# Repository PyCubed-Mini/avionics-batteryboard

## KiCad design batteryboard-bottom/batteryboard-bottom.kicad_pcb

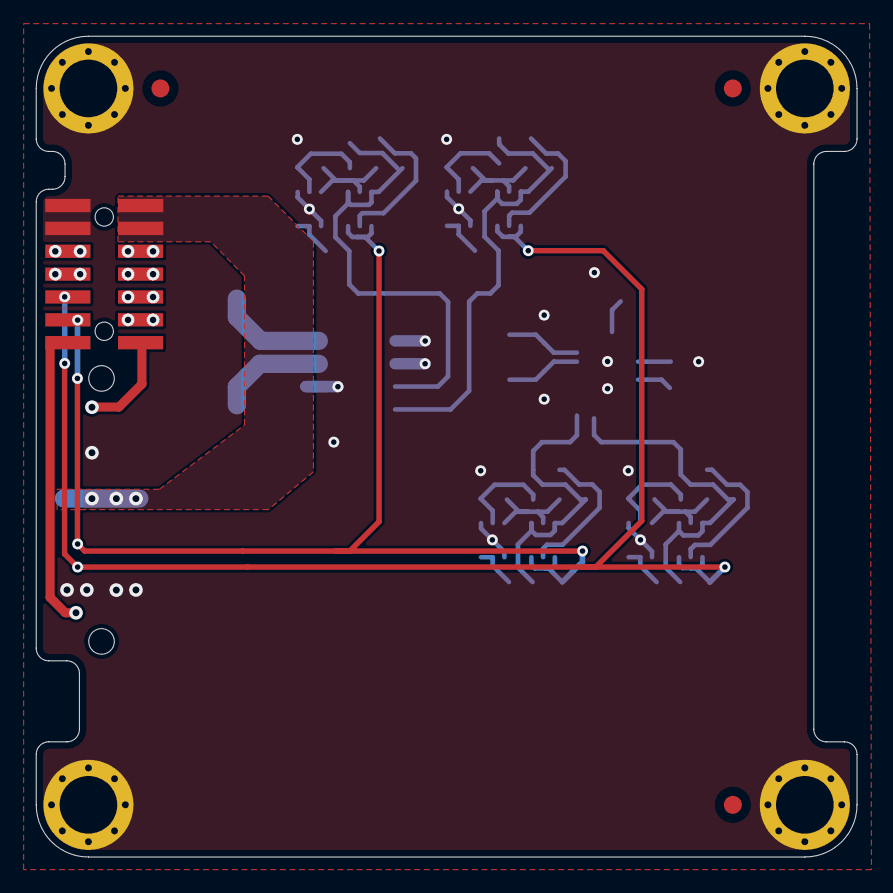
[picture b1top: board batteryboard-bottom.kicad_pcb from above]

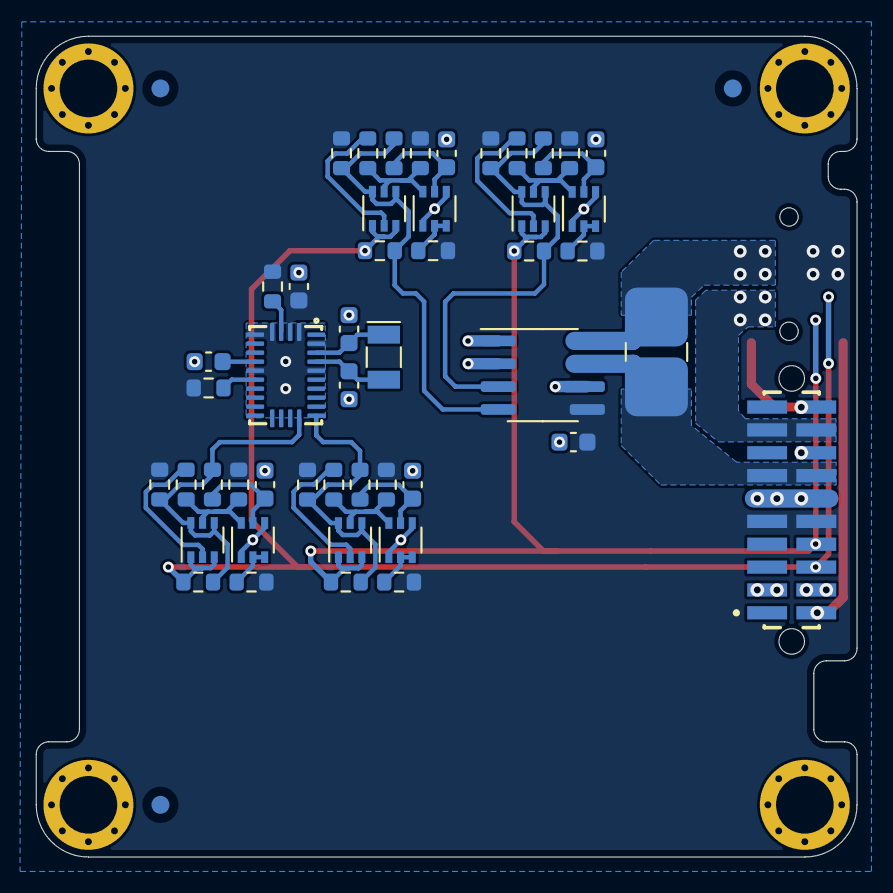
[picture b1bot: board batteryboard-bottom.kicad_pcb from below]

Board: 2 copper layers, 45.6 x 45.6 mm, 54 parts (48 on the bottom side), 35 nets.

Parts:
C1, C2, C8, C9: 10nF; C_0603_1608Metric
C3, C4, C5: 0.1uF; C_0603_1608Metric
C6, C7: 22pF; C_0603_1608Metric
H1, H2, H3, H4: MountingHole_Pad; MountingHole
J1: SFC-110-T2-X-D-A; SAMTEC_SFC-110-T2-X-D-A
J2: FTS-107-01-X-DV-A; SAMTEC-FTS-107-01-X-DV-A
Q1, Q3, Q5, Q7: NX3008NBKS; SOT-363_SC-70-6
Q2, Q4, Q6, Q8: MBT2222ADW1T1; SOT-363_SC-70-6
R1: 0.04R; R_2512_CurrentSense
R2, R7, R14, R21: 680R; R_0603_1608Metric
R3, R8, R15, R22: 100K; R_0603_1608Metric
R4, R5, R9, R10, R16, R17, R18, R19, R23, R24: 10K; R_0603_1608Metric
R6, R11, R20, R25: 200K; R_0603_1608Metric
R12, R13, R26, R27: DNI (0R); R_0603_1608Metric
Ref**: Val**; pycubed_mini_half
U1: INA219BxD; SOIC-8_3.9x4.9mm_P1.27mm
U2: BNO085; LGA-28
Y1: 32.768kHz/12.5pF; Crystal_SMD_MicroCrystal_CC7V-T1A-2Pin_3.2x1.5mm

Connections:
+3V3: C3.1, C4.1, J1.9, J1.10, J2.5, J2.7, R3.1, R4.1, R5.1, R8.1, R9.1, R10.1, R15.1, R16.2, R17.2, R18.1, R19.1, R22.1, R23.1, R24.1, U1.5 (VS), U2.3 (VDD), U2.28 (VDDIO)
BATT_N_SW: J1.11, J1.12, J2.2, J2.4
BATT_P: J1.17, J1.18, J2.10, J2.12
BATT_P_SENSE: J2.6, J2.8, R1.1, U1.8 (IN+)
BATT_P_SW: J1.13, J1.14, R1.2, U1.7 (IN-)
COIL5_N: J1.20, J2.14
COIL5_P: J1.2, J2.13
GND: C1.2, C2.2, C3.2, C4.2, C5.2, C6.1, C7.2, C8.2, C9.2, H1.1, H2.1, H3.1, H4.1, J1.3, J1.4, J1.16, J2.1, J2.3, Q1.1 (S2), Q1.4 (S1), Q3.1 (S2), Q3.4 (S1), Q5.1 (S2), Q5.4 (S1), Q7.1 (S2), Q7.4 (S1), U1.1 (A1), U1.2 (A0), U1.6 (GND), U2.2 (GND), U2.5 (PS1), U2.6 (PS0/WAKE), U2.10 (CLKSEL0), U2.25 (GNDIO)
IMU_RST: R17.1, U2.11 (NRST)
unnamed: Q1.6 (D1), Q2.5 (B2), R2.2, R4.2
unnamed: Q1.2 (G2), Q1.3 (D2), R3.2
unnamed: C1.1, Q1.5 (G1), R6.2
unnamed: Q2.2 (B1), R2.1
unnamed: Q3.6 (D1), Q4.5 (B2), R7.2, R9.2
unnamed: Q3.2 (G2), Q3.3 (D2), R8.2
unnamed: C2.1, Q3.5 (G1), R11.2
unnamed: Q4.2 (B1), R7.1
unnamed: Q5.6 (D1), Q6.5 (B2), R14.2, R18.2
unnamed: Q5.2 (G2), Q5.3 (D2), R15.2
unnamed: C8.1, Q5.5 (G1), R20.2
unnamed: Q6.2 (B1), R14.1
unnamed: Q7.6 (D1), Q8.5 (B2), R21.2, R23.2
unnamed: Q7.2 (G2), Q7.3 (D2), R22.2
unnamed: C9.1, Q7.5 (G1), R25.2
unnamed: Q8.2 (B1), R21.1
unnamed: R16.1, U2.4 (BOOTN)
unnamed: C5.1, U2.9 (CAP)
unnamed: C7.1, U2.26 (CLKSEL1/XOUT32), Y1.2
unnamed: C6.2, U2.27 (XIN32), Y1.1
SCL1: J1.6, J2.9, Q2.1 (E1), Q2.3 (C2), Q6.1 (E1), Q6.3 (C2), R12.2, R26.2
SCL_C_SENSE: Q2.4 (E2), Q2.6 (C1), R5.2, R6.1, R12.1, U1.4 (SCL)
SCL_IMU: Q6.4 (E2), Q6.6 (C1), R19.2, R20.1, R26.1, U2.19 (H_SCL/SCLK/RX)
SDA1: J1.8, J2.11, Q4.1 (E1), Q4.3 (C2), Q8.1 (E1), Q8.3 (C2), R13.2, R27.2
SDA_C_SENSE: Q4.4 (E2), Q4.6 (C1), R10.2, R11.1, R13.1, U1.3 (SDA)
SDA_IMU: Q8.4 (E2), Q8.6 (C1), R24.2, R25.1, R27.1, U2.20 (H_SDA/MISO/TX)

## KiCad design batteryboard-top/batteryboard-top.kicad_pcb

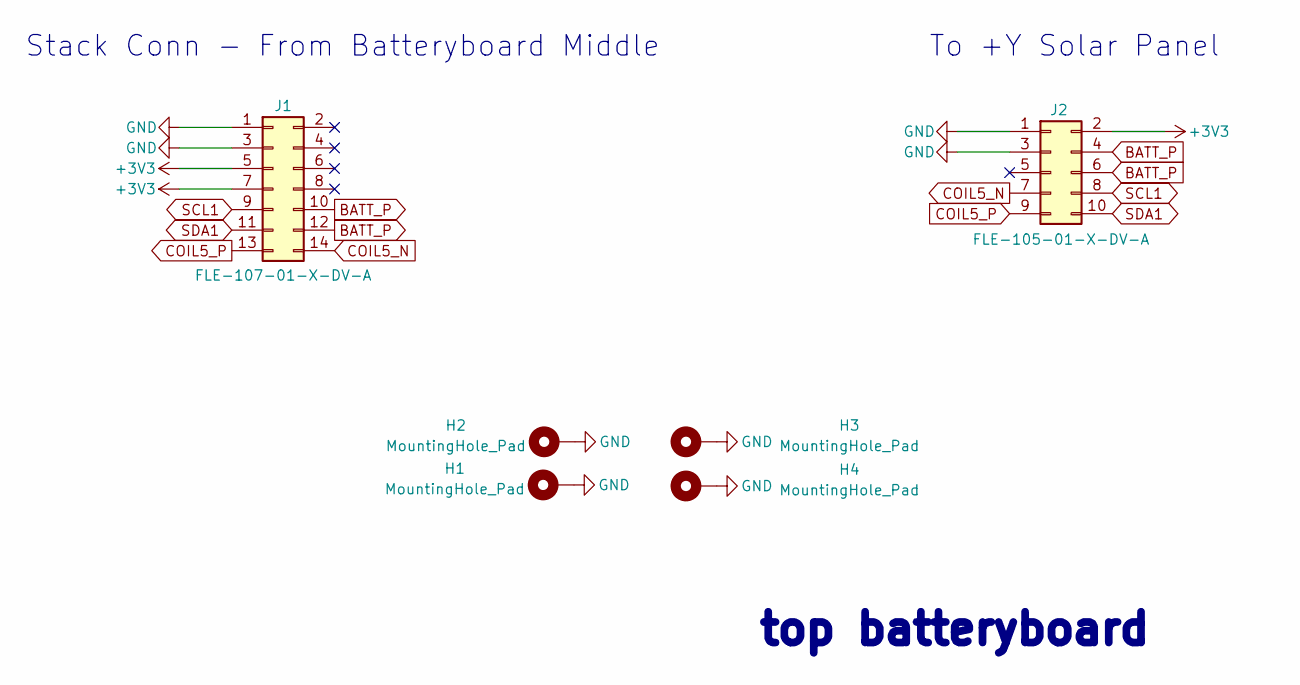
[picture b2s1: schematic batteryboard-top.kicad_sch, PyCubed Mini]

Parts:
H1, H2, H3, H4: MountingHole_Pad; MountingHole
J1: FLE-107-01-X-DV-A; SAMTEC_FLE-107-01-X-DV-A
J2: FLE-105-01-X-DV-A; SAMTEC_FLE-105-01-X-DV-A

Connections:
+3V3: J1.5, J1.7, J2.2
BATT_P: J1.10, J1.12, J2.4, J2.6
COIL5_N: J1.14, J2.7
COIL5_P: J1.13, J2.9
GND: H1.1, H2.1, H3.1, H4.1, J1.1, J1.3, J2.1, J2.3
SCL1: J1.9, J2.8
SDA1: J1.11, J2.10

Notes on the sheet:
To +Y Solar Panel
Stack Conn - From Batteryboard Middle
top batteryboard

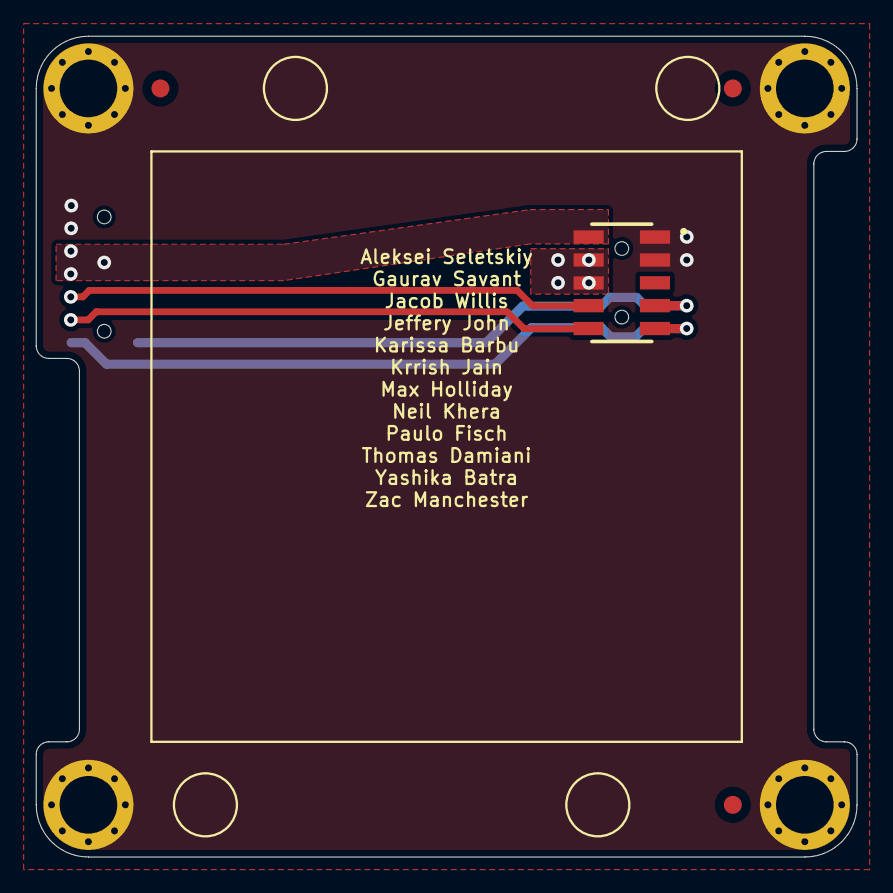
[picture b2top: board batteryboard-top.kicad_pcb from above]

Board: 2 copper layers, 45.6 x 45.6 mm, 7 parts (1 on the bottom side), 7 nets.

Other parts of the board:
Ref**: Val**; pycubed_mini_half

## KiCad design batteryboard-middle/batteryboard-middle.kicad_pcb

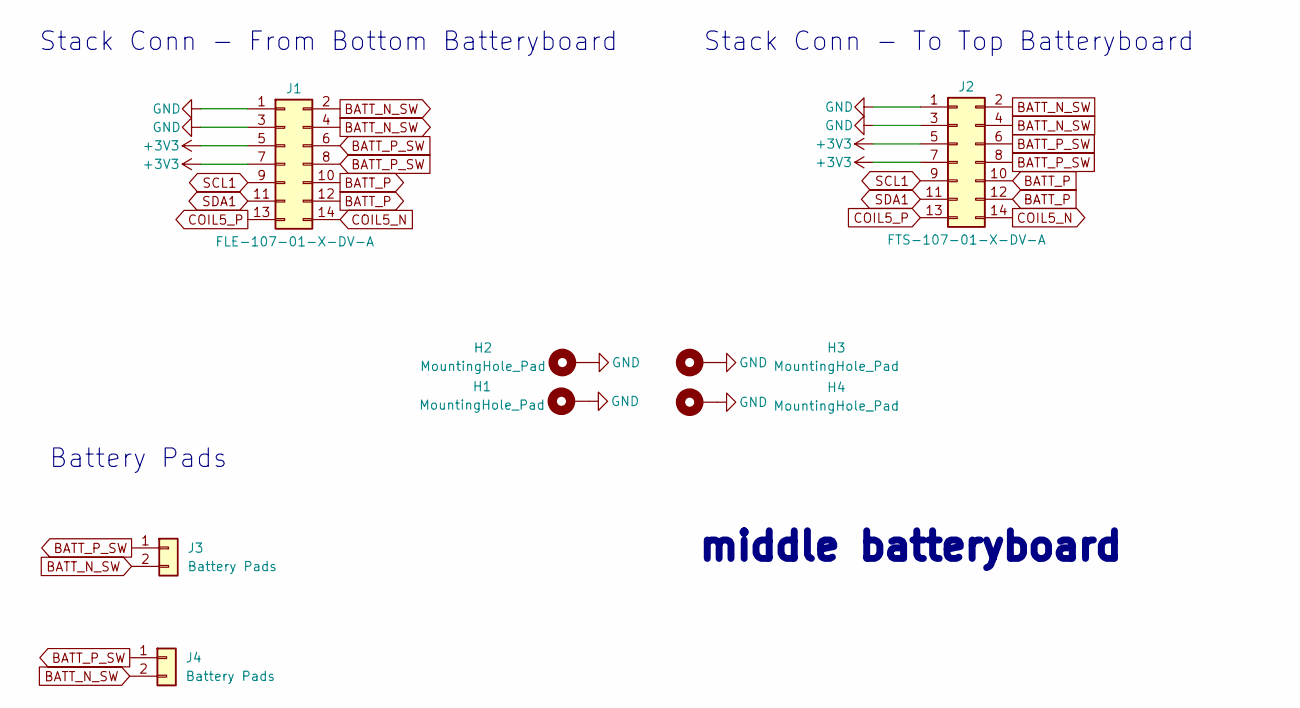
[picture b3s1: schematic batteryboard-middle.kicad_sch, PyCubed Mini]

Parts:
H1, H2, H3, H4: MountingHole_Pad; MountingHole
J1: FLE-107-01-X-DV-A; SAMTEC_FLE-107-01-X-DV-A
J2: FTS-107-01-X-DV-A; SAMTEC-FTS-107-01-X-DV-A
J3, J4: Battery Pads

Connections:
+3V3: J1.5, J1.7, J2.5, J2.7
BATT_N_SW: J1.2, J1.4, J2.2, J2.4, J3.2, J4.2
BATT_P: J1.10, J1.12, J2.10, J2.12
BATT_P_SW: J1.6, J1.8, J2.6, J2.8, J3.1, J4.1
COIL5_N: J1.14, J2.14
COIL5_P: J1.13, J2.13
GND: H1.1, H2.1, H3.1, H4.1, J1.1, J1.3, J2.1, J2.3
SCL1: J1.9, J2.9
SDA1: J1.11, J2.11

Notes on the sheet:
Stack Conn - To Top Batteryboard
Stack Conn - From Bottom Batteryboard
middle batteryboard
Battery Pads

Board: 2 copper layers, 9 parts (2 on the bottom side), 9 nets, no tracks yet.

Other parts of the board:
Ref**: Val**; pycubed_mini_half

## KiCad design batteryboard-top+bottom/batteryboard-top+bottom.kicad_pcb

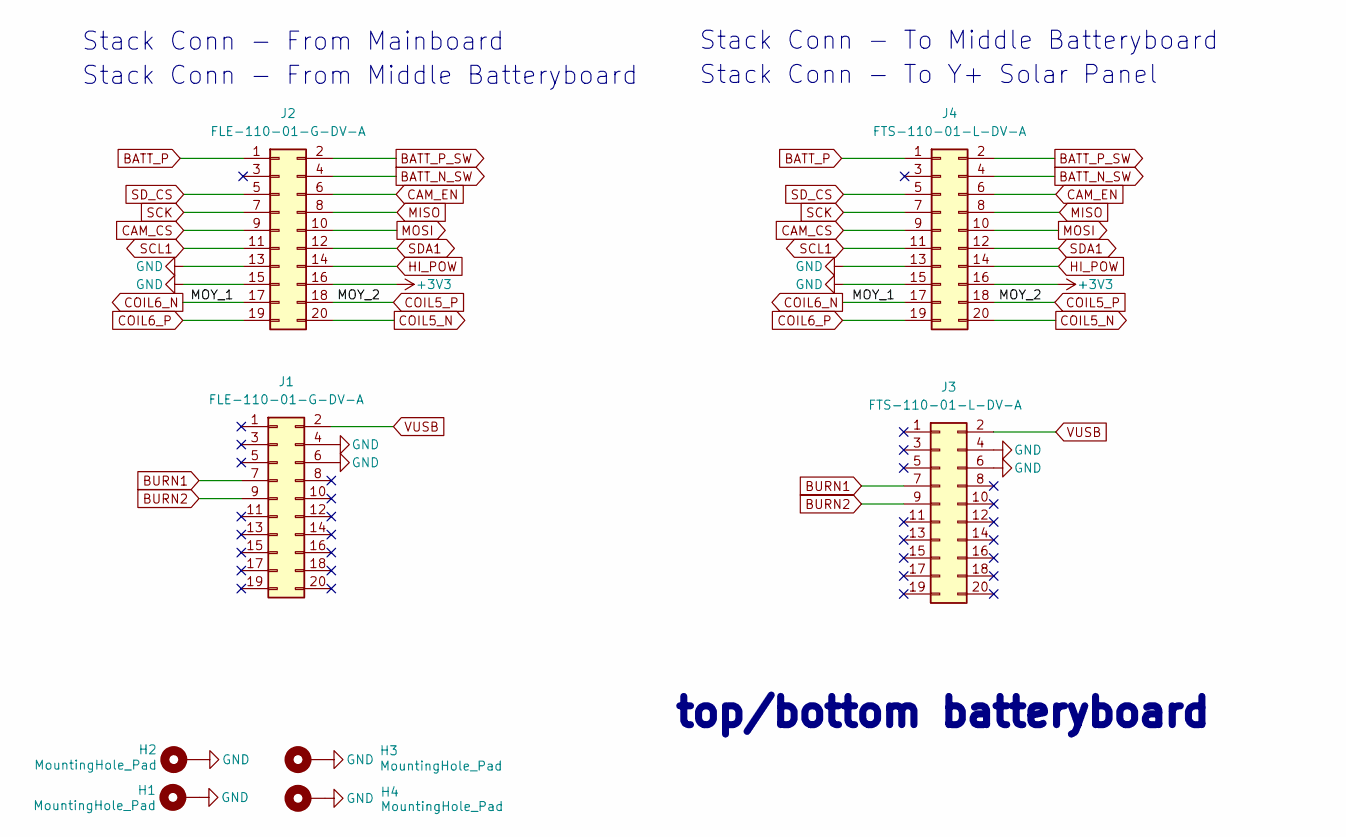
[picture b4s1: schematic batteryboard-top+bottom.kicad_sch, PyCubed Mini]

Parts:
H1, H2, H3, H4: MountingHole_Pad; MountingHole
J1, J2: FLE-110-01-G-DV-A; SAMTEC_FLE-110-01-G-DV-A
J3, J4: FTS-110-01-L-DV-A; SAMTEC-FTS-110-01-X-DV-A

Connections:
+3V3: J2.16, J4.16
BATT_N_SW: J2.4, J4.4
BATT_P: J2.1, J4.1
BATT_P_SW: J2.2, J4.2
BURN1: J1.7, J3.7
BURN2: J1.9, J3.9
CAM_CS: J2.9, J4.9
CAM_EN: J2.6, J4.6
COIL5_N: J2.20, J4.20
COIL5_P: J2.18, J4.18
COIL6_N: J2.17, J4.17
COIL6_P: J2.19, J4.19
GND: H1.1, H2.1, H3.1, H4.1, J1.4, J1.6, J2.13, J2.15, J3.4, J3.6, J4.13, J4.15
HI_POW: J2.14, J4.14
MISO: J2.8, J4.8
MOSI: J2.10, J4.10
SCK: J2.7, J4.7
SCL1: J2.11, J4.11
SDA1: J2.12, J4.12
SD_CS: J2.5, J4.5
VUSB: J1.2, J3.2

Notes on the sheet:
Stack Conn - From Mainboard
top/bottom batteryboard
Stack Conn - To Y+ Solar Panel
Stack Conn - To Middle Batteryboard
Stack Conn - From Middle Batteryboard

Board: 2 copper layers, 9 parts (2 on the bottom side), 21 nets, no tracks yet.

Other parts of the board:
Ref**: Val**; pycubed_mini_half

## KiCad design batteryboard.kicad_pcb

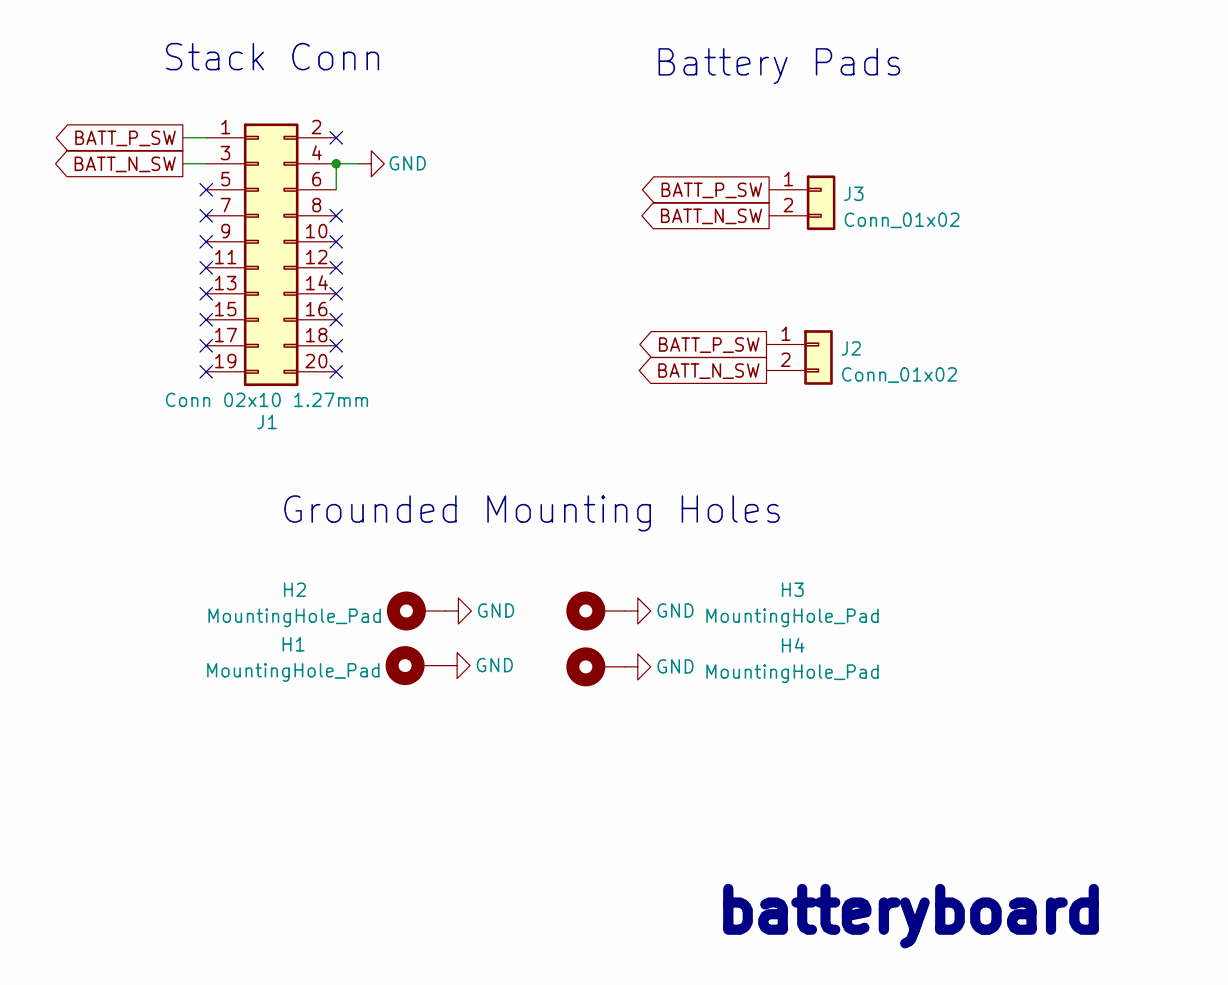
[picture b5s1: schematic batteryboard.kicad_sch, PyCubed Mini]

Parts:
H1, H2, H3, H4: MountingHole_Pad; MountingHole
J1: Conn 02x10 1.27mm; PinHeader_2x10_P1.27mm_Vertical
J2, J3: Conn_01x02; Battery Pads

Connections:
BATT_N_SW: J1.3, J2.2, J3.2
BATT_P_SW: J1.1, J2.1, J3.1
GND: H1.1, H2.1, H3.1, H4.1, J1.4, J1.6

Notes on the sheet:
Stack Conn
Grounded Mounting Holes
batteryboard
Battery Pads

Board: 2 copper layers, 7 parts (1 on the bottom side), 3 nets, no tracks yet.

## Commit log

2022-06-03 completed routing
2022-06-07 copied batteryboard files to batteryboard-middle
2022-06-07 renamed to batteryboard-middle
2022-06-07 copied middle board and modified schematic to match top board
2022-06-07 copied batteryboard-middle to create batteryboard-bottom
2022-06-07 modified connector arrangement
2022-06-07 labeled connections
2022-06-07 switch to 2x connectors for battery boards
2022-06-07 remove burn wire signals
2022-06-07 NC on pins 1 and 2 to match with -Y
2022-06-08 Added connectors and traces
2022-06-09 Added proper connectors and added traces
2022-06-09 Fixed design errors (some issues remain in middle) and fixed trace widths
2022-06-10 Fixes and cleanup
2022-06-10 add extra gnd via
2022-06-10 add + and - symbols
2022-06-14 Exported Gerbers
2022-06-27 Updated connector position on bottom batteryboard
2022-06-29 move +Y solar connector to make it less symmetric
2022-06-29 Updated connector position on top batteryboard
2022-06-29 Recheck boards and re-export models
2022-06-30 battery board top keepout and silkscreen
2022-07-01 Added +Y rail outline to top board silkscreen
2022-07-06 modified/standardized silkscreen
2022-07-06 Export New Gerbers
2022-08-21 v02 Updates
2022-09-06 B1/03 updates
2022-09-08 Widened Power Traces, Added Notch for Antenna Cable Routing
2022-09-09 Added credits to top batteryboard
2022-09-13 Exported Files
2022-09-13 Fixed Broken Merge
2022-10-09 Some changes
2022-10-09 B2/01 Updates
2022-10-09 Minor Schematic Updates
2022-11-09 Minor updates and exported STEP / BOM
2022-11-10 DFM updates
2022-11-11 Export Gerbers
2023-02-19 Updated batteryboards for Rev B3/01
2023-02-25 Added battery current sensing to bottom batteryboard
2023-02-26 Updated credits. Removed gerbers from repo
2023-04-26 Rev B3/02 updates
2023-04-26 Updated BOMs and STEP files
2024-02-01 Rev B3/03 updates
